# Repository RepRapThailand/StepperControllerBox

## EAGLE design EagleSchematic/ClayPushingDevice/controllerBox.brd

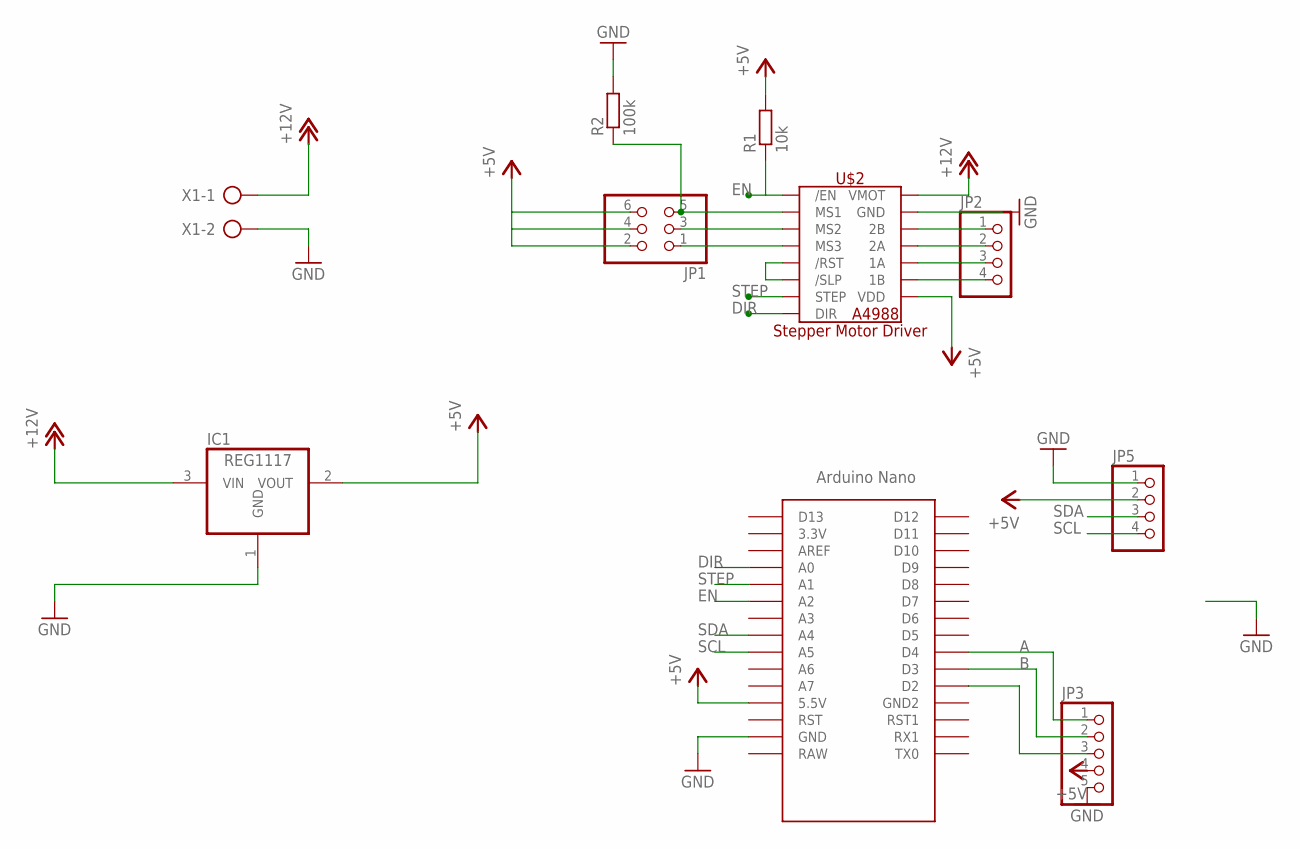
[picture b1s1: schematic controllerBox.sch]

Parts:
IC1: REG1117; SOT223
JP1: PINHD-2X3; 2X03
JP2, JP5: PINHD-1X4; 1X04
JP3: PINHD-1X5; 1X05
R1: 10k; 0207/10
R2: 100k; 0207/10
U$1: NANO
U$2: A4988_STEP
X1: AK300/2

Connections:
+5V: IC1.2 (VOUT), JP1.2, JP1.4, JP1.6, JP3.4, JP5.2, R1.2, U$1.5V (5.5V), U$2.VDD
+12V: IC1.3 (VIN), U$2.VMOT, X1.1
A: JP3.1, U$1.D4
B: JP3.2, U$1.D3
DIR: U$1.A0, U$2.DIR
EN: R1.1, U$1.A2, U$2./EN
GND: IC1.1 (GND), JP3.5, JP5.1, R2.2, U$1.GND, U$2.GND, U$2.GND2 (GND), X1.2
unnamed: U$2./RST, U$2./SLP
unnamed: JP1.5, R2.1, U$2.MS1
unnamed: JP1.3, U$2.MS2
unnamed: JP1.1, U$2.MS3
unnamed: JP2.1, U$2.2B
unnamed: JP2.2, U$2.2A
unnamed: JP2.3, U$2.1A
unnamed: JP2.4, U$2.1B
unnamed: JP3.3, U$1.D2
SCL: JP5.4, U$1.A5
SDA: JP5.3, U$1.A4
STEP: U$1.A1, U$2.STEP

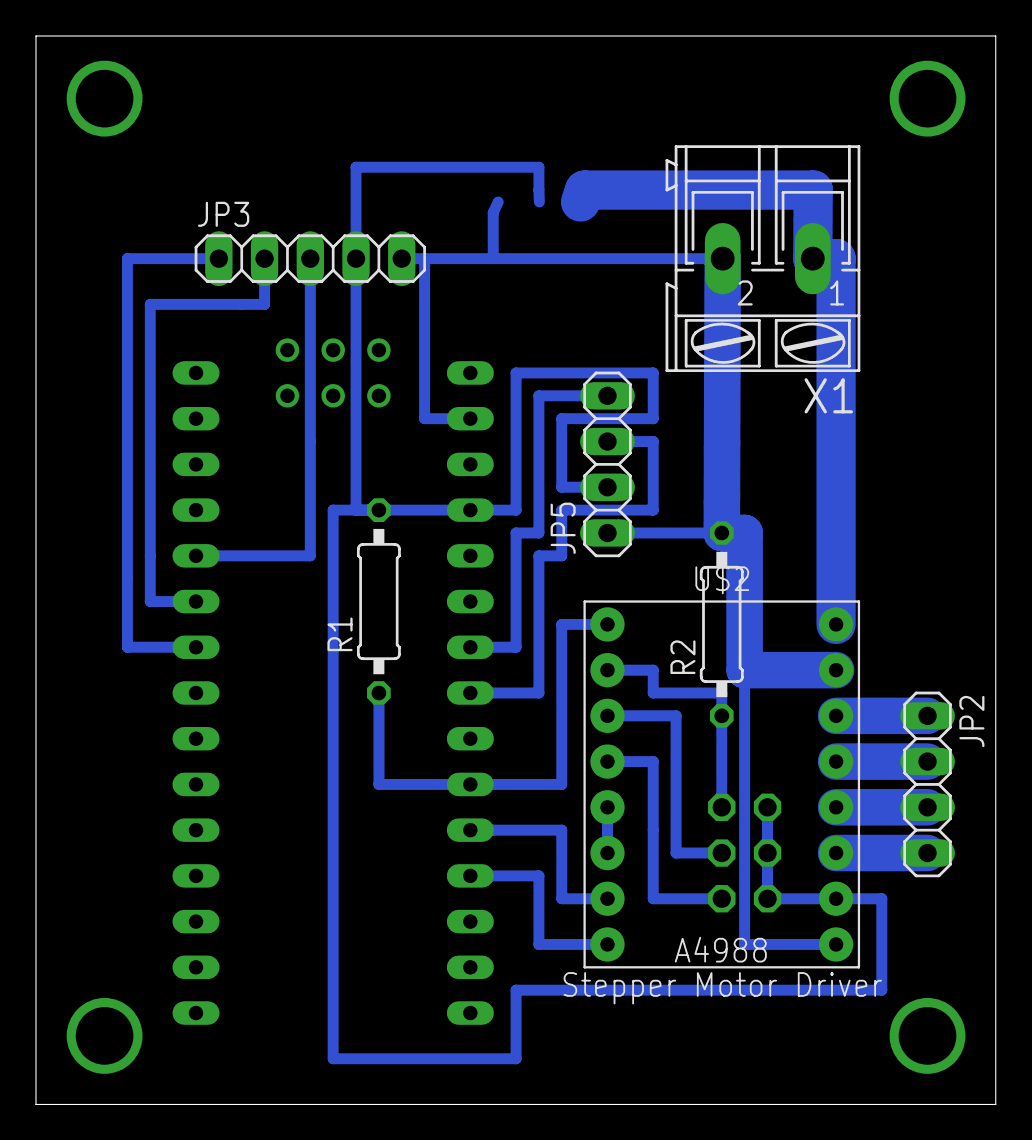
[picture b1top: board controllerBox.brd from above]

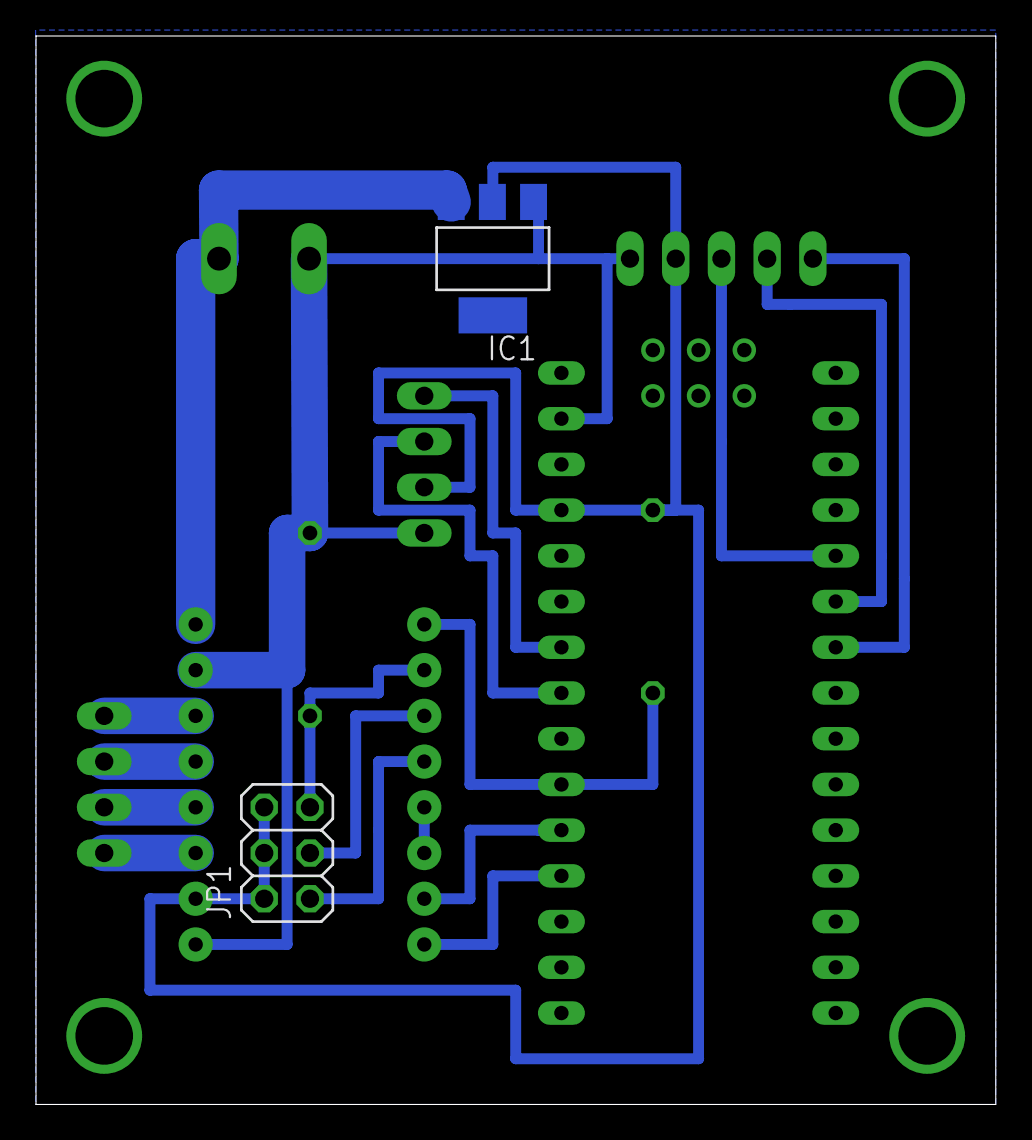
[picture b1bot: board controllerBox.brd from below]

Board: 2 copper layers, 53.3 x 59.4 mm, 10 parts (2 on the bottom side), 19 nets.

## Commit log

2019-06-27 Add .gitignore and .gitattributes.
2019-06-27 Add project files.
2019-06-27 rename folder
2019-07-04 add schematic
2019-07-12 hihi
